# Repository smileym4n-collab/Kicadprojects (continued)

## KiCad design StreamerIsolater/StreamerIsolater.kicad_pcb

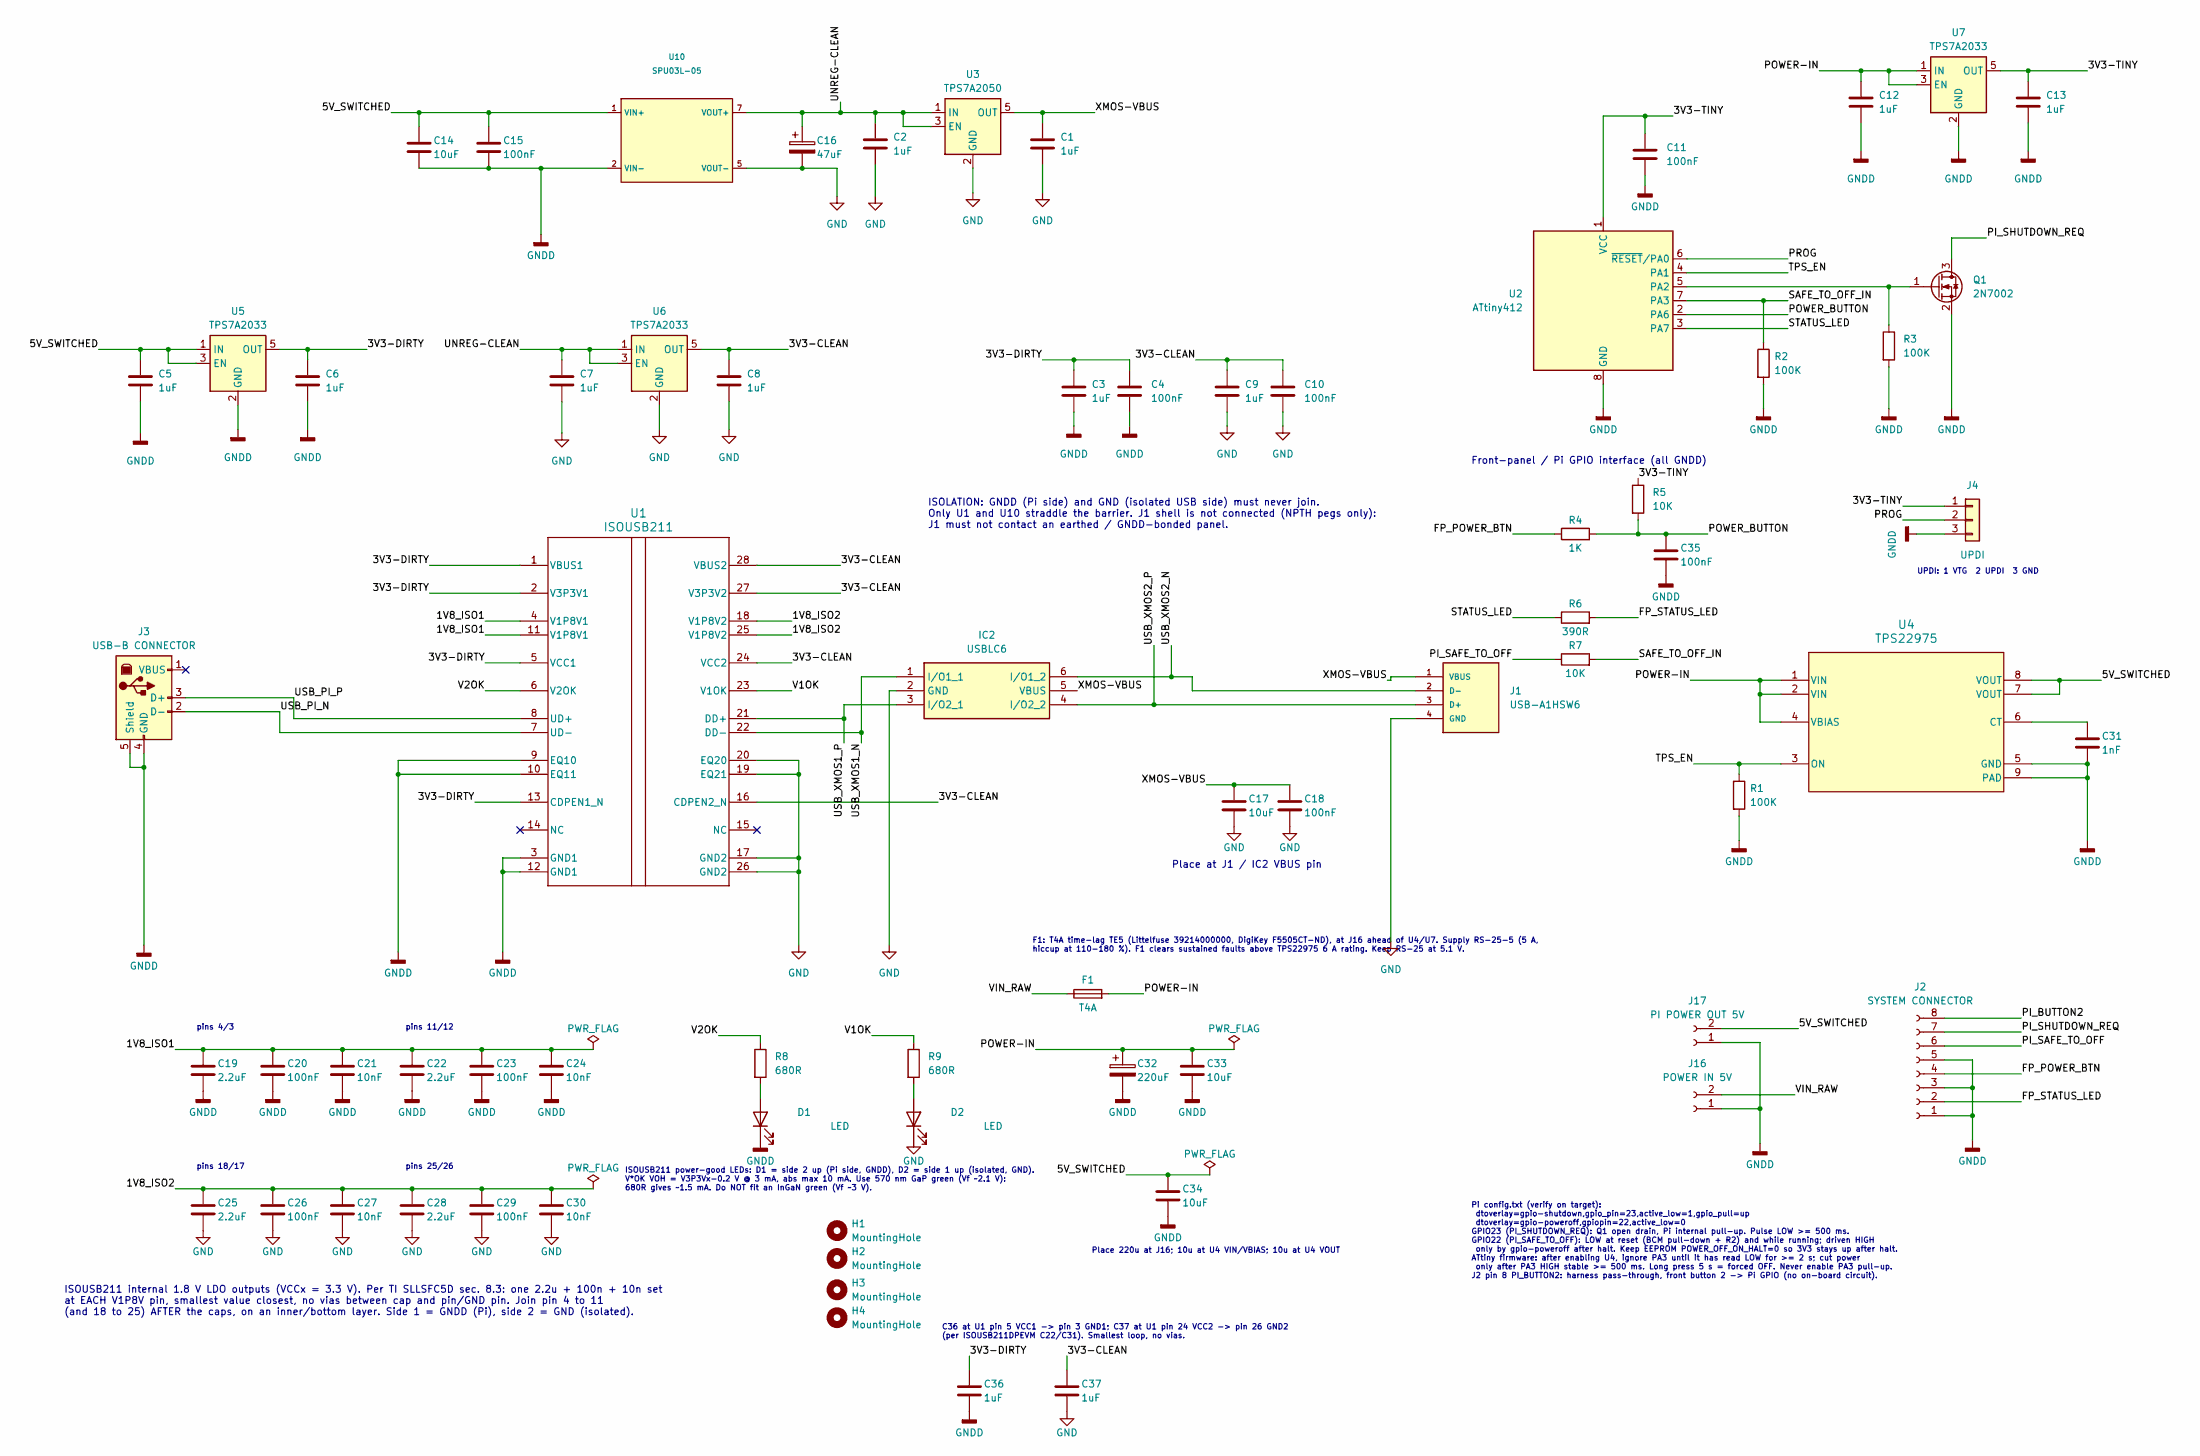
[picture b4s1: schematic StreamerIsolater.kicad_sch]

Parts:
C1, C2, C3, C5, C6, C7, C8, C9, C12, C13, C36, C37: 1uF; C_0805_2012Metric_Pad1.18x1.45mm_HandSolder; Manufacturer_Part_Number CL21B105KAFNNNG; DigiKey Part Number 1276-6469-1-ND
C4, C10, C11, C15, C18, C20, C23, C26, C29, C35: 100nF; C_0603_1608Metric_Pad1.08x0.95mm_HandSolder; Manufacturer_Part_Number C0603C104M5RACTU; DigiKey Part Number 399-C0603C104M5RACTUCT-ND
C14, C17, C33, C34: 10uF; C_1206_3216Metric_Pad1.33x1.80mm_HandSolder
C16: 47uF; CP_Radial_D5.0mm_P2.00mm
C19, C22, C25, C28: 2.2uF; C_0805_2012Metric_Pad1.18x1.45mm_HandSolder
C21, C24, C27, C30: 10nF; C_0805_2012Metric_Pad1.18x1.45mm_HandSolder
C31: 1nF; C_0805_2012Metric_Pad1.18x1.45mm_HandSolder
C32: 220uF; CP_Radial_D6.3mm_P2.50mm
D1, D2: LED; LED_0805_2012Metric_Pad1.15x1.40mm_HandSolder; Manufacturer_Part_Number APT2012SGC
F1: T4A; Fuse_Littelfuse_395Series; Manufacturer_Part_Number 39214000000; DigiKey Part Number F5505CT-ND
H1, H2, H3, H4: MountingHole; MountingHole_3.2mm_M3
IC2: USBLC6; SOT-23-6_Handsoldering; Mouser Part Number 511-USBLC6-2SC6
J1: USB-A1HSW6; PARTREV A
J2: SYSTEM CONNECTOR; JST_XH_B8B-XH-A_1x08_P2.50mm_Vertical
J3: USB-B CONNECTOR; USBC
J4: UPDI; PinHeader_1x03_P2.54mm_Vertical
J16: POWER IN 5V; Molex_KK-396_A-41791-0002_1x02_P3.96mm_Vertical
J17: PI POWER OUT 5V; Molex_KK-396_A-41791-0002_1x02_P3.96mm_Vertical
Q1: 2N7002; SOT-23
R1, R2, R3: 100K; R_0805_2012Metric_Pad1.20x1.40mm_HandSolder
R4: 1K; R_0805_2012Metric_Pad1.20x1.40mm_HandSolder
R5, R7: 10K; R_0805_2012Metric_Pad1.20x1.40mm_HandSolder
R6: 390R; R_0805_2012Metric_Pad1.20x1.40mm_HandSolder
R8, R9: 680R; R_0805_2012Metric_Pad1.20x1.40mm_HandSolder
U1: ISOUSB211
U2: ATtiny412; SOIC-8_3.9x4.9mm_P1.27mm
U3: TPS7A2050; SOT-23-5
U4: TPS22975; DSG0008B
U5, U6, U7: TPS7A2033; SOT-23-5
U10: SPU03L-05; SPU03L_05_SIP7

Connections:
/1V8_ISO1: C19.1, C20.1, C21.1, C22.1, C23.1, C24.1, U1.4 (V1P8V1), U1.11 (V1P8V1)
/1V8_ISO2: C25.1, C26.1, C27.1, C28.1, C29.1, C30.1, U1.18 (V1P8V2), U1.25 (V1P8V2)
/3V3-CLEAN: C8.1, C9.1, C10.1, C37.1, U1.16 (CDPEN2_N), U1.24 (VCC2), U1.27 (V3P3V2), U1.28 (VBUS2), U6.5 (OUT)
/3V3-DIRTY: C3.1, C4.1, C6.1, C36.1, U1.1 (VBUS1), U1.2 (V3P3V1), U1.5 (VCC1), U1.13 (CDPEN1_N), U5.5 (OUT)
/3V3-TINY: C11.1, C13.1, J4.1, R5.1, U2.1 (VCC), U7.5 (OUT)
/5V_SWITCHED: C5.1, C14.1, C15.1, C34.1, J17.2, U4.7 (VOUT), U4.8 (VOUT), U5.1 (IN), U5.3 (EN), U10.1 (VIN+)
/FP_POWER_BTN: J2.4, R4.1
/FP_STATUS_LED: J2.2, R6.2
/PI_BUTTON2: J2.8
/PI_SAFE_TO_OFF: J2.6, R7.1
/PI_SHUTDOWN_REQ: J2.7, Q1.3 (D)
/POWER-IN: C12.1, C32.1, C33.1, F1.2, U4.1 (VIN), U4.2 (VIN), U4.4 (VBIAS), U7.1 (IN), U7.3 (EN)
/POWER_BUTTON: C35.1, R4.2, R5.2, U2.2 (PA6)
/PROG: J4.2, U2.6 (~RESET/PA0)
/SAFE_TO_OFF_IN: R2.1, R7.2, U2.7 (PA3)
/STATUS_LED: R6.1, U2.3 (PA7)
/TPS_EN: R1.1, U2.4 (PA1), U4.3 (ON)
/UNREG-CLEAN: C2.1, C7.1, C16.1, U3.1 (IN), U3.3 (EN), U6.1 (IN), U6.3 (EN), U10.7 (VOUT+)
/USB_PI_N: J3.2 (D-), U1.7 (UD-)
/USB_PI_P: J3.3 (D+), U1.8 (UD+)
/USB_XMOS1_N: IC2.1 (I/O1_1), U1.22 (DD-)
/USB_XMOS1_P: IC2.3 (I/O2_1), U1.21 (DD+)
/USB_XMOS2_N: IC2.6 (I/O1_2), J1.2 (D-)
/USB_XMOS2_P: IC2.4 (I/O2_2), J1.3 (D+)
/V1OK: R9.1, U1.23 (V1OK)
/V2OK: R8.1, U1.6 (V2OK)
/VIN_RAW: F1.1, J16.2
/XMOS-VBUS: C1.1, C17.1, C18.1, IC2.5 (VBUS), J1.1 (VBUS), U3.5 (OUT)
GND: C1.2, C2.2, C7.2, C8.2, C9.2, C10.2, C16.2, C17.2, C18.2, C25.2, C26.2, C27.2, C28.2, C29.2, C30.2, C37.2, D2.1 (K), IC2.2 (GND), J1.4 (GND), U1.17 (GND2), U1.19 (EQ21), U1.20 (EQ20), U1.26 (GND2), U3.2 (GND), U6.2 (GND), U10.5 (VOUT-)
GNDD: C3.2, C4.2, C5.2, C6.2, C11.2, C12.2, C13.2, C14.2, C15.2, C19.2, C20.2, C21.2, C22.2, C23.2, C24.2, C31.2, C32.2, C33.2, C34.2, C35.2, C36.2, D1.1 (K), J2.1, J2.3, J2.5, J3.4 (GND), J3.5 (Shield), J4.3, J16.1, J17.1, Q1.2 (S), R1.2, R2.2, R3.2, U1.3 (GND1), U1.9 (EQ10), U1.10 (EQ11), U1.12 (GND1), U2.8 (GND), U4.5 (GND), U4.9 (PAD), U4.V, U5.2 (GND), U7.2 (GND), U10.2 (VIN-)
unnamed: D1.2 (A), R8.2
unnamed: D2.2 (A), R9.2
unnamed: Q1.1 (G), R3.1, U2.5 (PA2)
unnamed: C31.1, U4.6 (CT)

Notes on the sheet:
C36 at U1 pin 5 VCC1 -> pin 3 GND1; C37 at U1 pin 24 VCC2 -> pin 26 GND2 (per ISOUSB211DPEVM C22/C31). Smallest loop, no vias.
UPDI: 1 VTG 2 UPDI 3 GND
pins 18/17
ISOUSB211 internal 1.8 V LDO outputs (VCCx = 3.3 V). Per TI SLLSFC5D sec. 8.3: one 2.2u + 100n + 10n set at EACH V1P8V pin, smallest value closest, no vias between cap and pin/GND pin. Join pin 4 to 11 (and 18 to 25) AFTER the caps, on an inner/bottom layer. Side 1 = GNDD (Pi), side 2 = GND (isolat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
Place at J1 / IC2 VBUS pin
F1: T4A time-lag TE5 (Littelfuse 39214000000, DigiKey F5505CT-ND), at J16 ahead of U4/U7. Supply RS-25-5 (5 A, hiccup at 110-180 %). F1 clears sustained faults above TPS22975 6 A rating. Keep RS-25 at 5.1 V.
Front-panel / Pi GPIO interface (all GNDD)
Place 220u at J16; 10u at U4 VIN/VBIAS; 10u at U4 VOUT
pins 25/26
Pi config.txt (verify on target): dtoverlay=gpio-shutdown,gpio_pin=23,active_low=1,gpio_pull=up dtoverlay=gpio-poweroff,gpiopin=22,active_low=0 GPIO23 (PI_SHUTDOWN_REQ): Q1 open drain, Pi internal pull-up. Pulse LOW >= 500 ms. GPIO22 (PI_SAFE_TO_OFF): LOW at reset (BCM pull-down + R2) and while run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
pins 11/12
ISOUSB211 power-good LEDs: D1 = side 2 up (Pi side, GNDD), D2 = side 1 up (isolated, GND). V*OK VOH = V3P3Vx-0.2 V @ 3 mA, abs max 10 mA. Use 570 nm GaP green (Vf ~2.1 V): 680R gives ~1.5 mA. Do NOT fit an InGaN green (Vf ~3 V).
ISOLATION: GNDD (Pi side) and GND (isolated USB side) must never join. Only U1 and U10 straddle the barrier. J1 shell is not connected (NPTH pegs only): J1 must not contact an earthed / GNDD-bonded panel.
pins 4/3

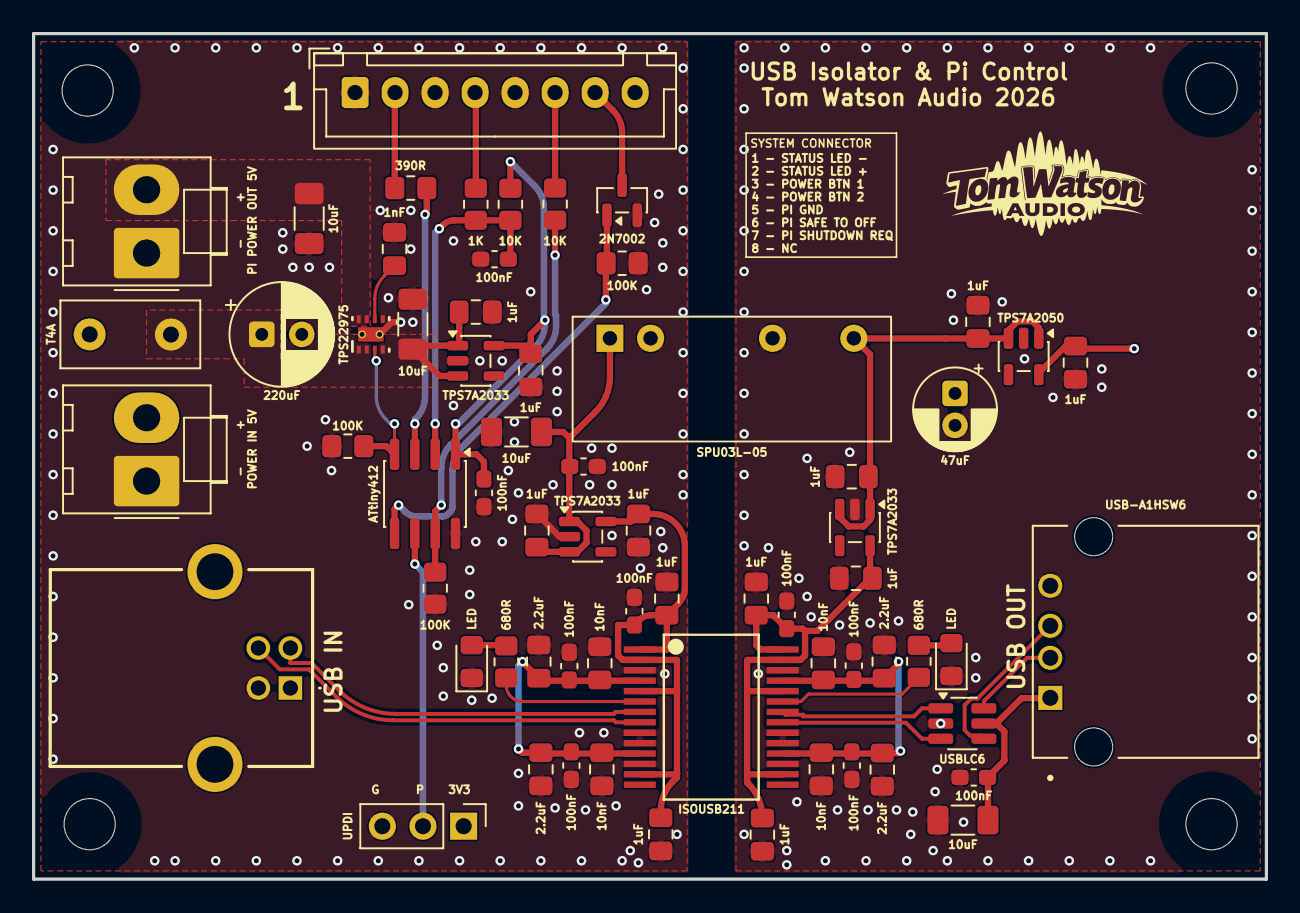
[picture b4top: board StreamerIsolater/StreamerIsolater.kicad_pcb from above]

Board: 4 copper layers, 77.0 x 52.8 mm, 69 parts (0 on the bottom side), 33 nets.

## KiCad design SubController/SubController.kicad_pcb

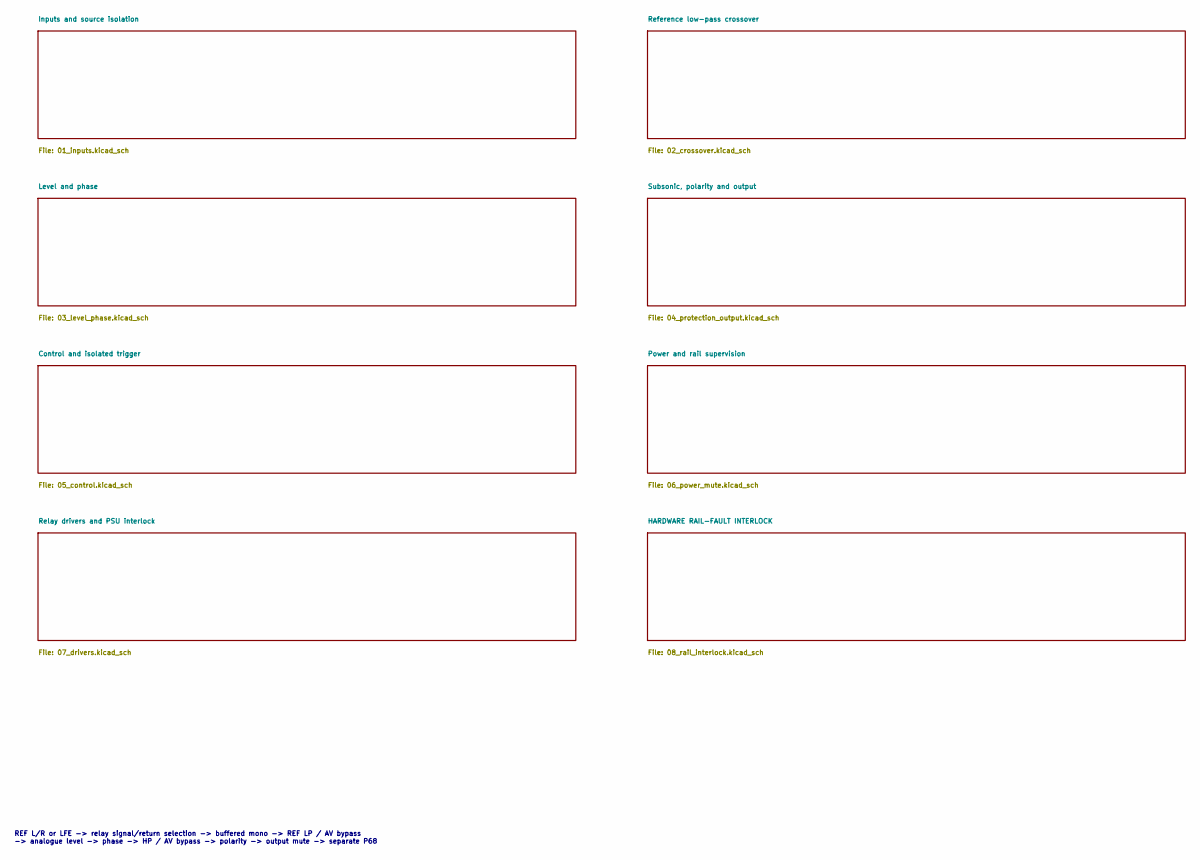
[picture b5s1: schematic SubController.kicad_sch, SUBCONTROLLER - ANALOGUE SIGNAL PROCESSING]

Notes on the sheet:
REF L/R or LFE -> relay signal/return selection -> buffered mono -> REF LP / AV bypass -> analogue level -> phase -> HP / AV bypass -> polarity -> output mute -> separate P68

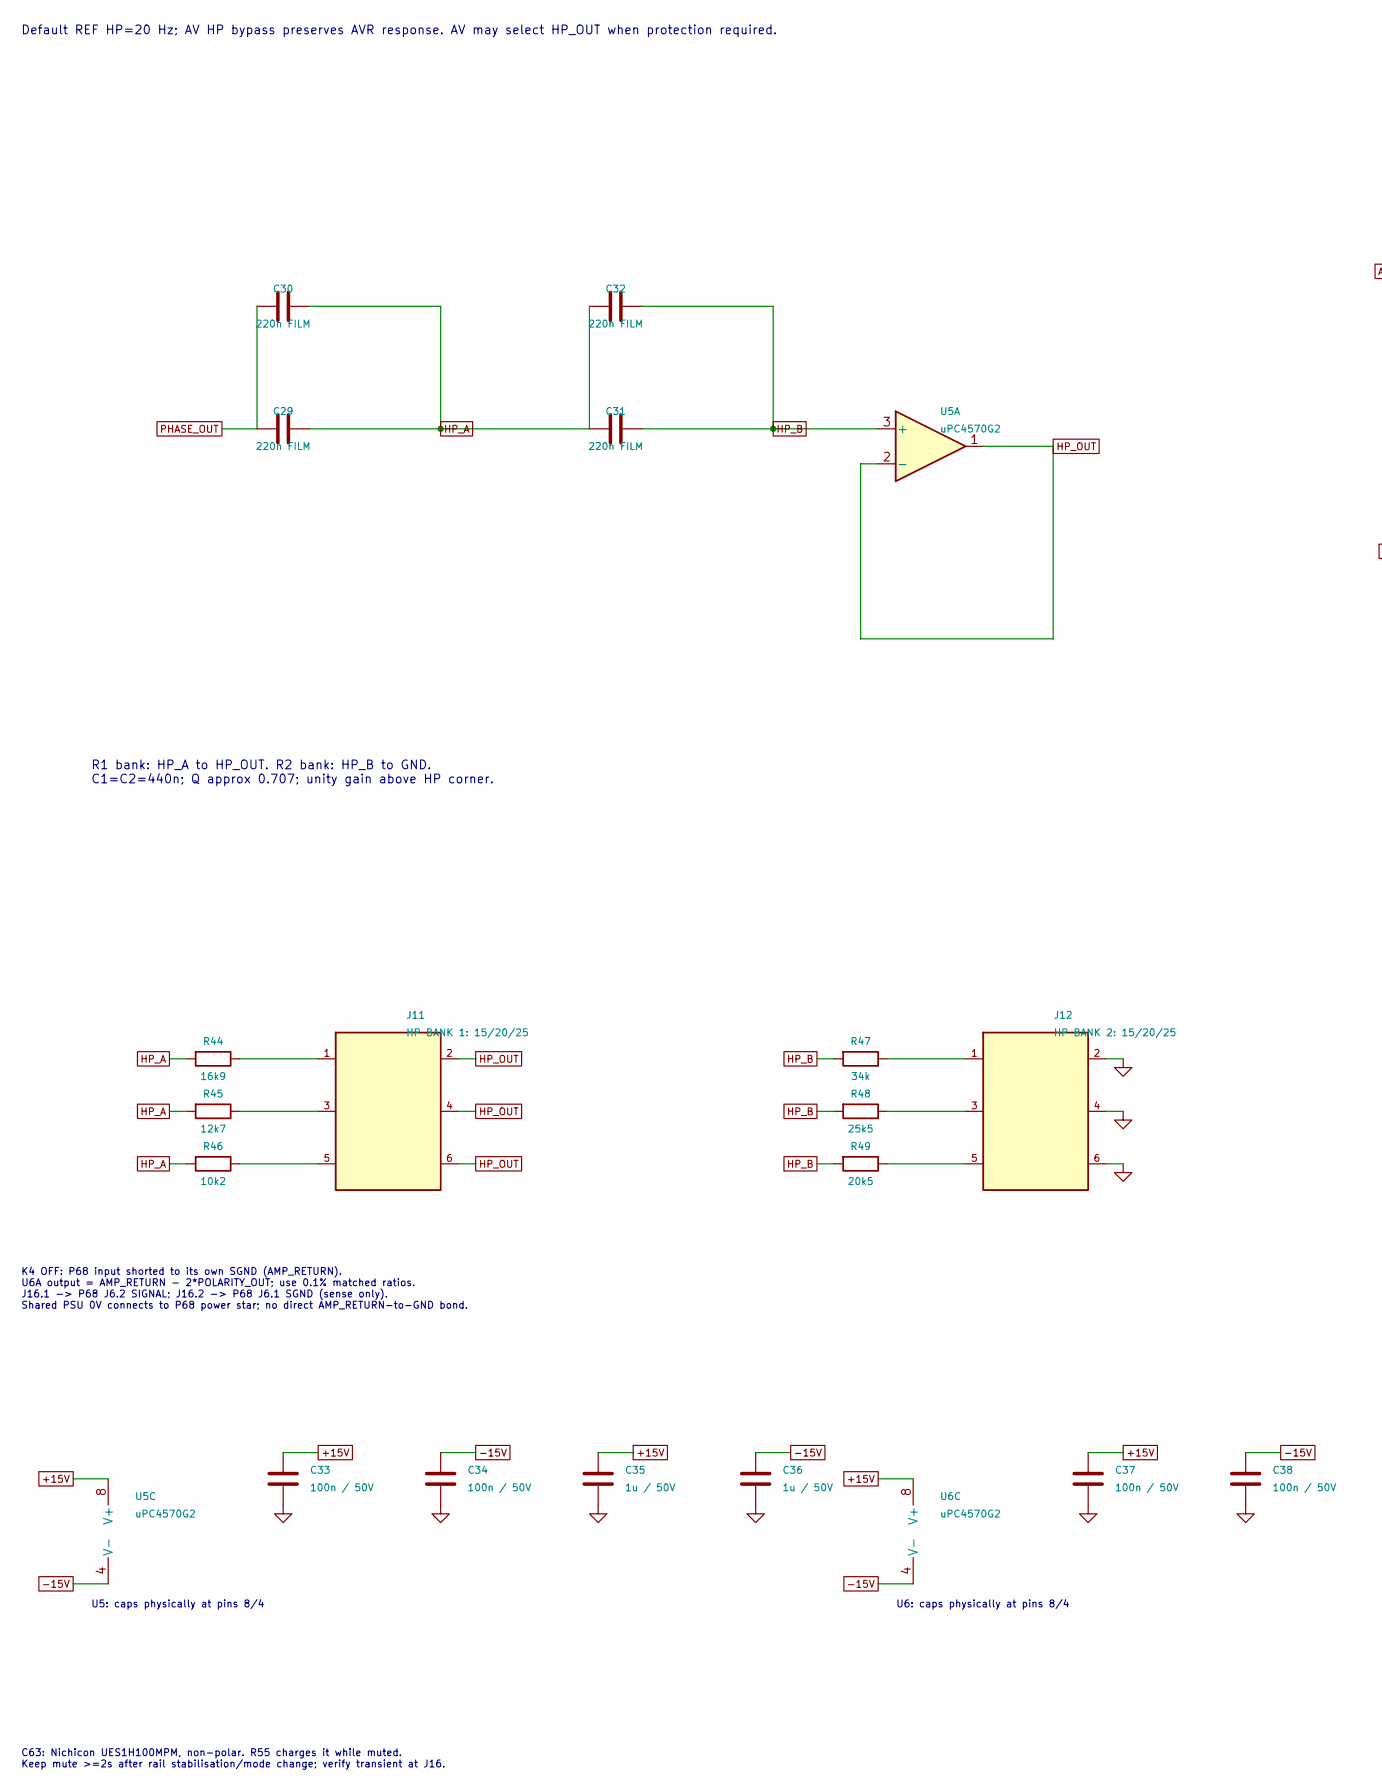
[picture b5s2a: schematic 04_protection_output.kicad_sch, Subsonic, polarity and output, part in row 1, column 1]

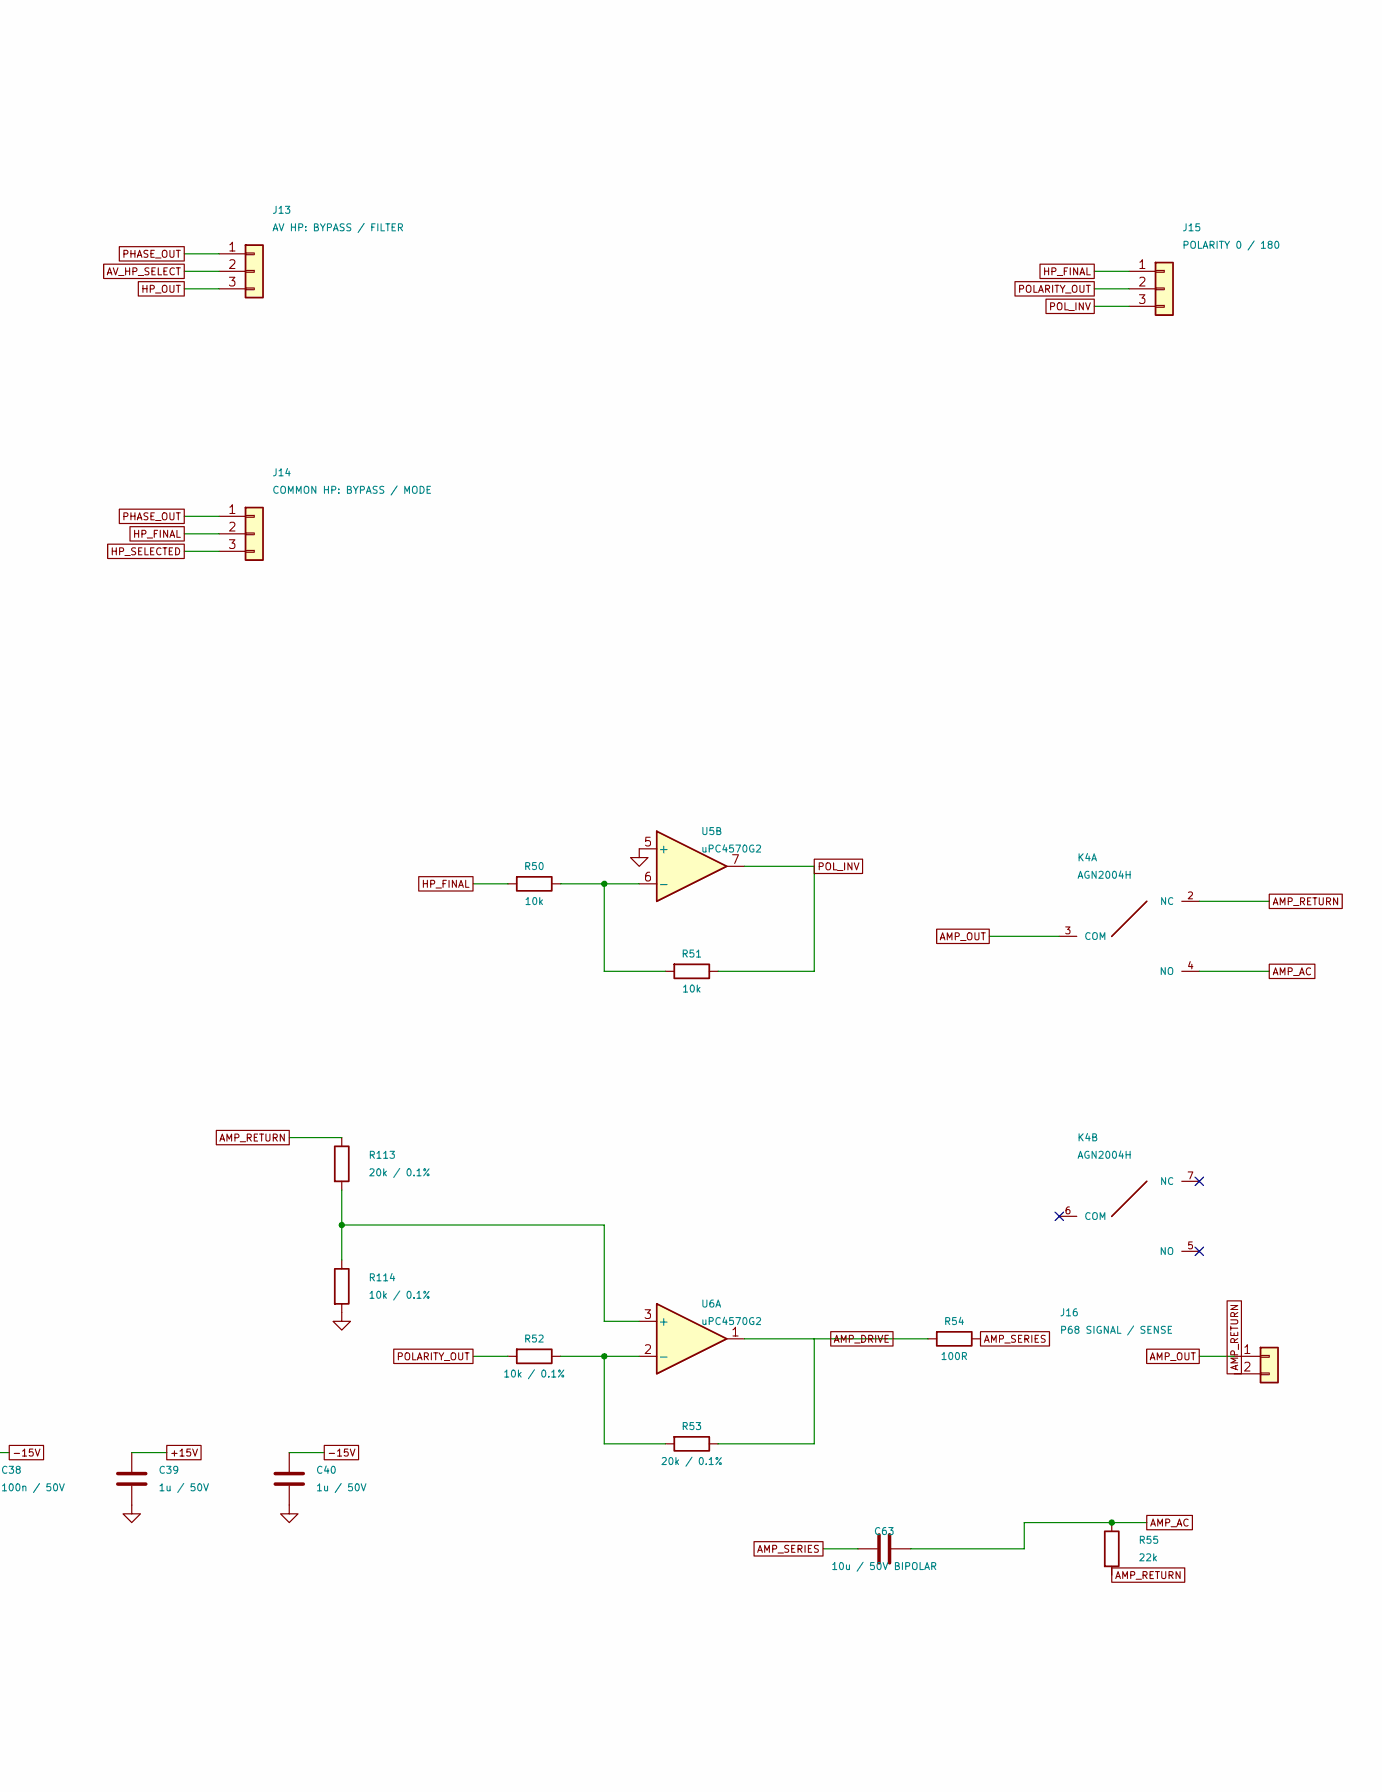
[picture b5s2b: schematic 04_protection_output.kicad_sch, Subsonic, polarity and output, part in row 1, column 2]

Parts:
C29, C30, C31, C32: 220n FILM; Film_7.2x2.5mm_P5.00mm
C33, C34, C37, C38: 100n / 50V; C_1206_3216Metric
C35, C36, C39, C40: 1u / 50V; C_1206_3216Metric
C63: 10u / 50V BIPOLAR; C_NP_Radial_D8.0mm_P3.50mm
J11: HP BANK 1: 15/20/25; PinHeader_2x03_P2.54mm_Vertical
J12: HP BANK 2: 15/20/25; PinHeader_2x03_P2.54mm_Vertical
J13: AV HP: BYPASS / FILTER; PinHeader_1x03_P2.54mm_Vertical
J14: COMMON HP: BYPASS / MODE; PinHeader_1x03_P2.54mm_Vertical
J15: POLARITY 0 / 180; PinHeader_1x03_P2.54mm_Vertical
J16: P68 SIGNAL / SENSE; PinHeader_1x02_P2.54mm_Vertical
K4: AGN2004H; Relay_DPDT_Panasonic_AGN2004H
R44: 16k9; R_0805_2012Metric
R45: 12k7; R_0805_2012Metric
R46: 10k2; R_0805_2012Metric
R47: 34k; R_0805_2012Metric
R48: 25k5; R_0805_2012Metric
R49: 20k5; R_0805_2012Metric
R50, R51: 10k; R_0805_2012Metric
R52, R114: 10k / 0.1%; R_0805_2012Metric
R53, R113: 20k / 0.1%; R_0805_2012Metric
R54: 100R; R_0805_2012Metric
R55: 22k; R_0805_2012Metric
U5, U6: uPC4570G2; SOP-8_uPC4570G2_4.4x5.2mm_P1.27mm

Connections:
+15V: C33.1, C35.1, C37.1, C39.1, U5.8 (V+), U6.8 (V+); also elsewhere on the board
-15V: C34.1, C36.1, C38.1, C40.1, U5.4 (V-), U6.4 (V-); also elsewhere on the board
AMP_AC: C63.1, K4.4 (NO), R55.1
AMP_DRIVE: R53.1, R54.2, U6.1
AMP_OUT: J16.1, K4.3 (COM); also elsewhere on the board
AMP_RETURN: J16.2, K4.2 (NC), R55.2, R113.1
AMP_SERIES: C63.2, R54.1
AV_HP_SELECT: J13.2; also elsewhere on the board
GND: C33.2, C34.2, C35.2, C36.2, C37.2, C38.2, C39.2, C40.2, J12.2, J12.4, J12.6, R114.2, U5.5 (+); also elsewhere on the board
HP_A: C29.1, C30.1, C31.2, C32.2, R44.2, R45.2, R46.2
HP_B: C31.1, C32.1, R47.2, R48.2, R49.2, U5.3 (+)
HP_FINAL: J14.2, J15.1, R50.2
HP_OUT: J11.2, J11.4, J11.6, J13.3, U5.1, U5.2 (-); also elsewhere on the board
HP_SELECTED: J14.3; also elsewhere on the board
unnamed: J11.1, R44.1
unnamed: J11.3, R45.1
unnamed: J11.5, R46.1
unnamed: J12.1, R47.1
unnamed: J12.3, R48.1
unnamed: J12.5, R49.1
unnamed: R50.1, R51.2, U5.6 (-)
unnamed: R113.2, R114.1, U6.3 (+)
unnamed: R52.1, R53.2, U6.2 (-)
PHASE_OUT: C29.2, C30.2, J13.1, J14.1; also elsewhere on the board
POLARITY_OUT: J15.2, R52.2
POL_INV: J15.3, R51.1, U5.7

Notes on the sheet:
Default REF HP=20 Hz; AV HP bypass preserves AVR response. AV may select HP_OUT when protection required.
R1 bank: HP_A to HP_OUT. R2 bank: HP_B to GND. C1=C2=440n; Q approx 0.707; unity gain above HP corner.
C63: Nichicon UES1H100MPM, non-polar. R55 charges it while muted. Keep mute >=2s after rail stabilisation/mode change; verify transient at J16.
U5: caps physically at pins 8/4
U6: caps physically at pins 8/4
K4 OFF: P68 input shorted to its own SGND (AMP_RETURN). U6A output = AMP_RETURN - 2*POLARITY_OUT; use 0.1% matched ratios. J16.1 -> P68 J6.2 SIGNAL; J16.2 -> P68 J6.1 SGND (sense only). Shared PSU 0V connects to P68 power star; no direct AMP_RETURN-to-GND bond.

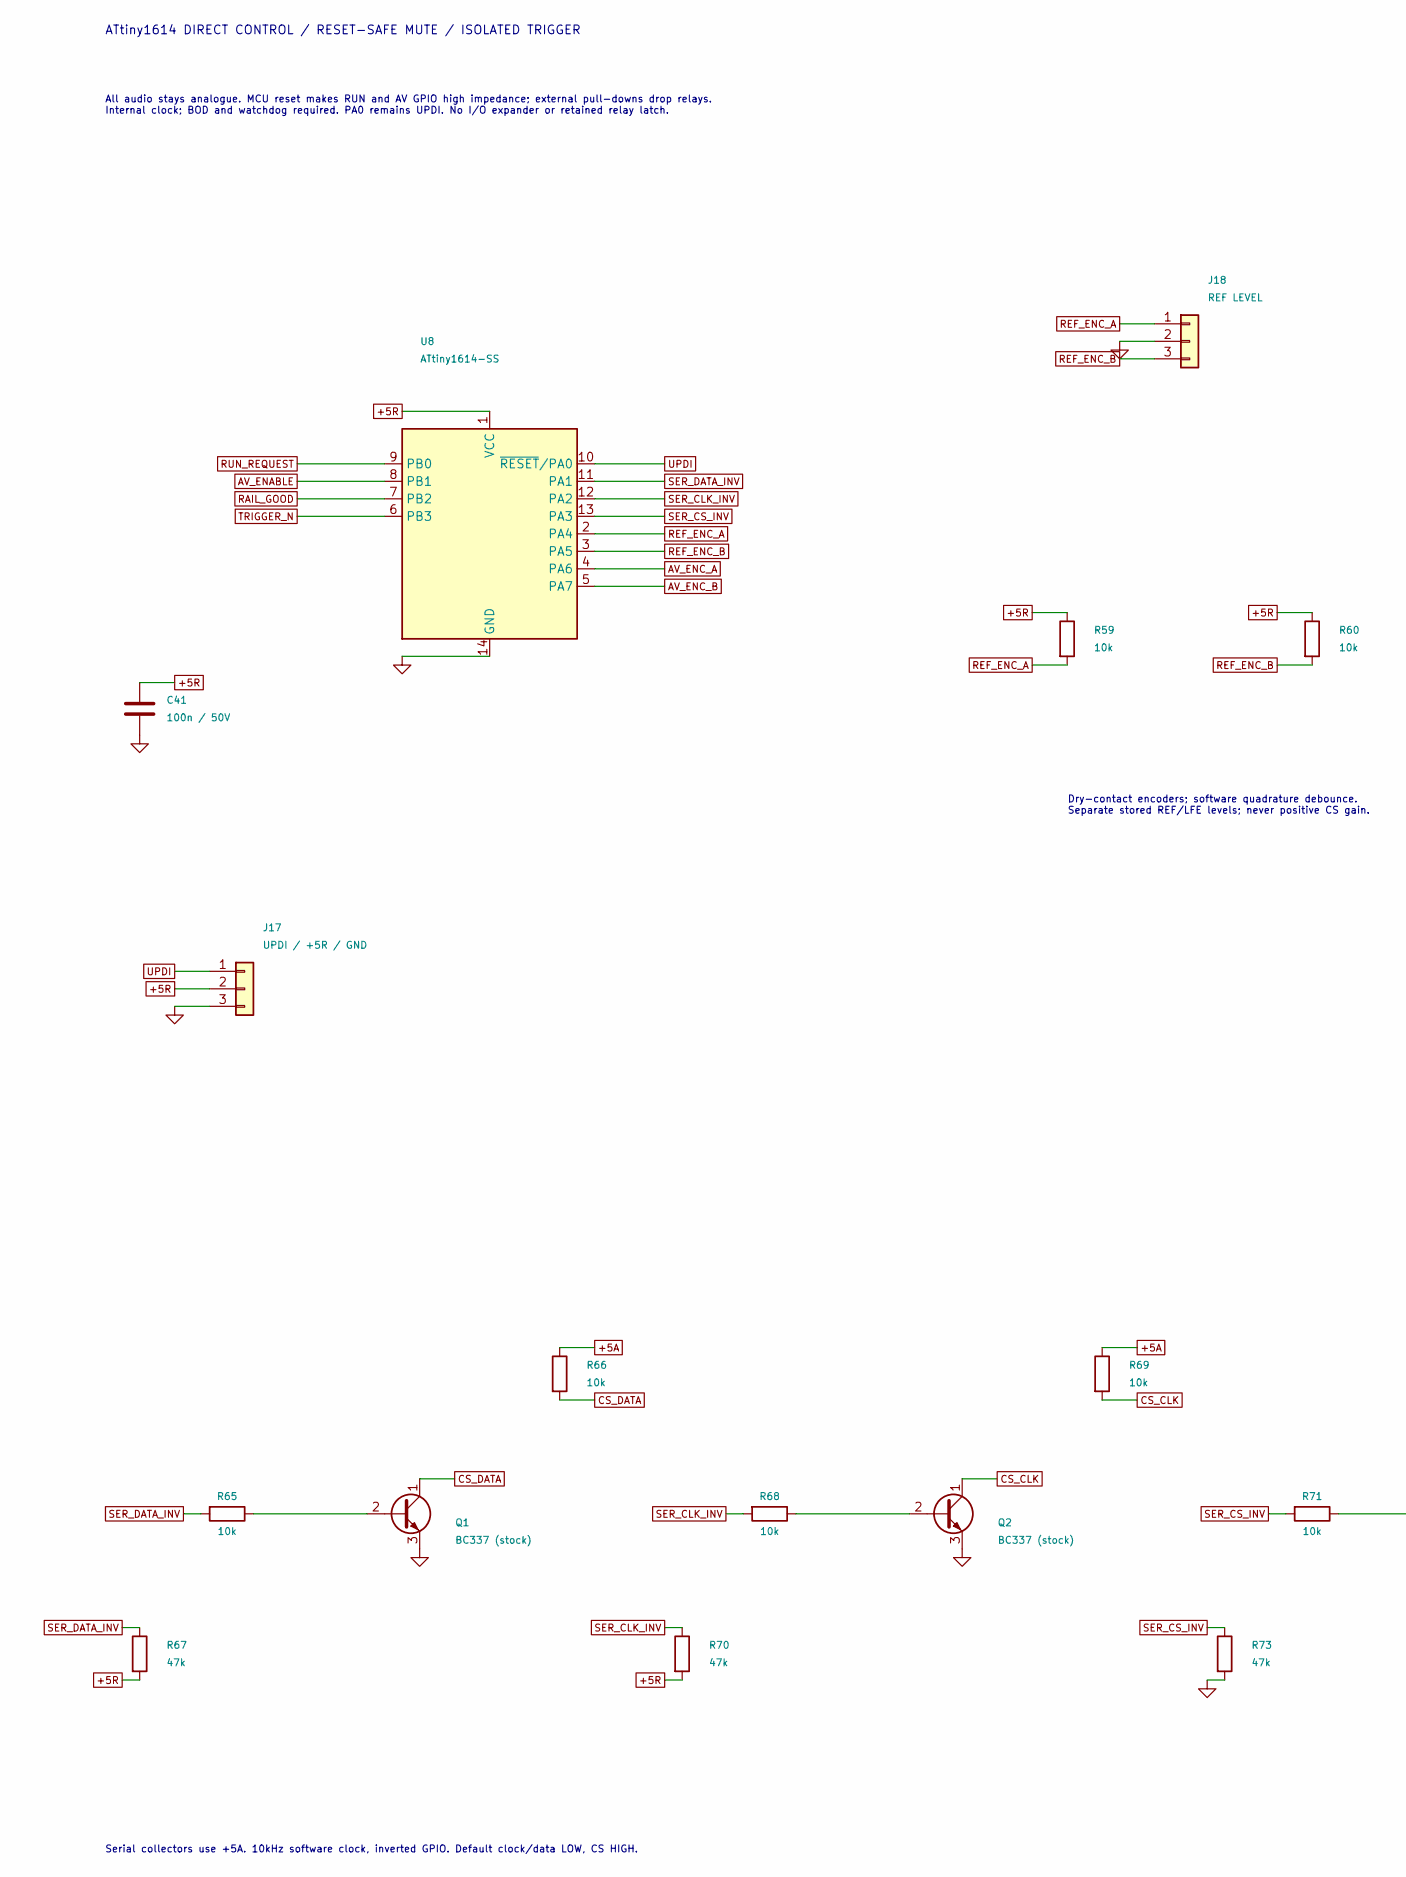
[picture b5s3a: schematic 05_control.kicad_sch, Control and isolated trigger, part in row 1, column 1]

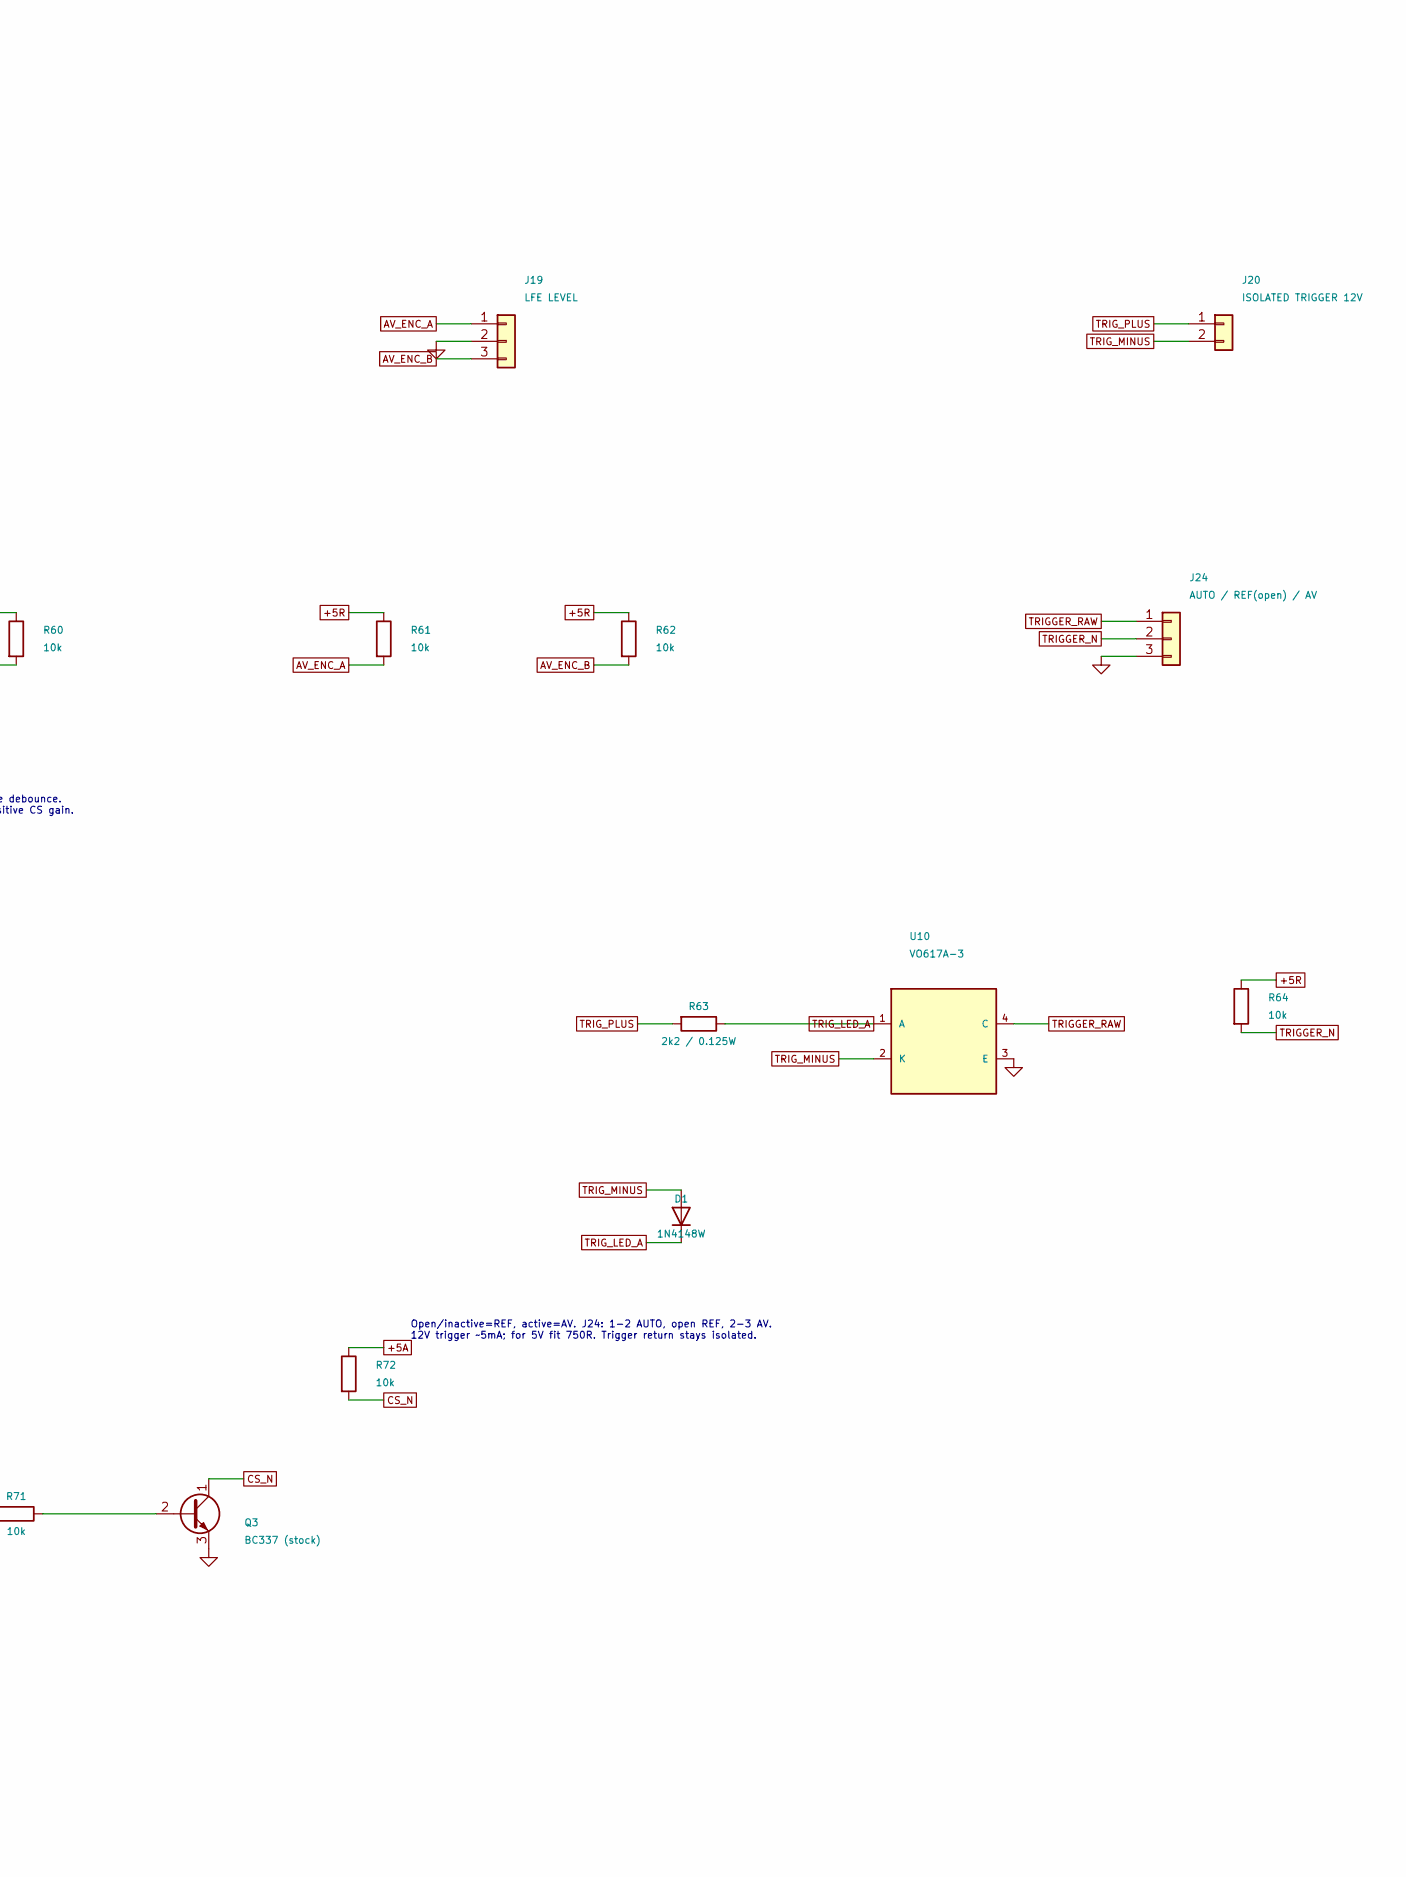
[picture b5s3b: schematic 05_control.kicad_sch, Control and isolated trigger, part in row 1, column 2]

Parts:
C41: 100n / 50V; C_1206_3216Metric
D1: 1N4148W; D_SOD-123
J17: UPDI / +5R / GND; PinHeader_1x03_P2.54mm_Vertical
J18: REF LEVEL; PinHeader_1x03_P2.54mm_Vertical
J19: LFE LEVEL; PinHeader_1x03_P2.54mm_Vertical
J20: ISOLATED TRIGGER 12V; PinHeader_1x02_P2.54mm_Vertical
J24: AUTO / REF(open) / AV; PinHeader_1x03_P2.54mm_Vertical
Q1, Q2, Q3: BC337 (stock); TO-92_Inline
R59, R60, R61, R62, R64, R65, R66, R68, R69, R71, R72: 10k; R_0805_2012Metric
R63: 2k2 / 0.125W; R_0805_2012Metric
R67, R70, R73: 47k; R_0805_2012Metric
U8: ATtiny1614-SS; SOIC-14_3.9x8.7mm_P1.27mm
U10: VO617A-3; DIP-4_W7.62mm

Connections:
+5A: R66.1, R69.1, R72.1; also elsewhere on the board
+5R: C41.1, J17.2, R59.1, R60.1, R61.1, R62.1, R64.1, R67.2, R70.2, U8.1 (VCC); also elsewhere on the board
AV_ENABLE: U8.8 (PB1); also elsewhere on the board
AV_ENC_A: J19.1, R61.2, U8.4 (PA6)
AV_ENC_B: J19.3, R62.2, U8.5 (PA7)
CS_CLK: Q2.1 (C), R69.2; also elsewhere on the board
CS_DATA: Q1.1 (C), R66.2; also elsewhere on the board
CS_N: Q3.1 (C), R72.2; also elsewhere on the board
GND: C41.2, J17.3, J18.2, J19.2, J24.3, Q1.3 (E), Q2.3 (E), Q3.3 (E), R73.2, U8.14 (GND), U10.3 (E); also elsewhere on the board
unnamed: Q1.2 (B), R65.1
unnamed: Q2.2 (B), R68.1
unnamed: Q3.2 (B), R71.1
RAIL_GOOD: U8.7 (PB2); also elsewhere on the board
REF_ENC_A: J18.1, R59.2, U8.2 (PA4)
REF_ENC_B: J18.3, R60.2, U8.3 (PA5)
RUN_REQUEST: U8.9 (PB0); also elsewhere on the board
SER_CLK_INV: R68.2, R70.1, U8.12 (PA2)
SER_CS_INV: R71.2, R73.1, U8.13 (PA3)
SER_DATA_INV: R65.2, R67.1, U8.11 (PA1)
TRIGGER_N: J24.2, R64.2, U8.6 (PB3); also elsewhere on the board
TRIGGER_RAW: J24.1, U10.4 (C)
TRIG_LED_A: D1.1 (K), R63.1, U10.1 (A)
TRIG_MINUS: D1.2 (A), J20.2, U10.2 (K)
TRIG_PLUS: J20.1, R63.2
UPDI: J17.1, U8.10 (~RESET/PA0)

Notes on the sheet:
All audio stays analogue. MCU reset makes RUN and AV GPIO high impedance; external pull-downs drop relays. Internal clock; BOD and watchdog required. PA0 remains UPDI. No I/O expander or retained relay latch.
Open/inactive=REF, active=AV. J24: 1-2 AUTO, open REF, 2-3 AV. 12V trigger ~5mA; for 5V fit 750R. Trigger return stays isolated.
Dry-contact encoders; software quadrature debounce. Separate stored REF/LFE levels; never positive CS gain.
Serial collectors use +5A. 10kHz software clock, inverted GPIO. Default clock/data LOW, CS HIGH.
ATtiny1614 DIRECT CONTROL / RESET-SAFE MUTE / ISOLATED TRIGGER
